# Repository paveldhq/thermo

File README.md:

# thermo
Open project for thermo cam based on ESP32 and MLX90640

`thermo.sh` options:
 - `reset` - resets all internal arduino and php state and re-downloads needed content
 - `build` - builds sketch

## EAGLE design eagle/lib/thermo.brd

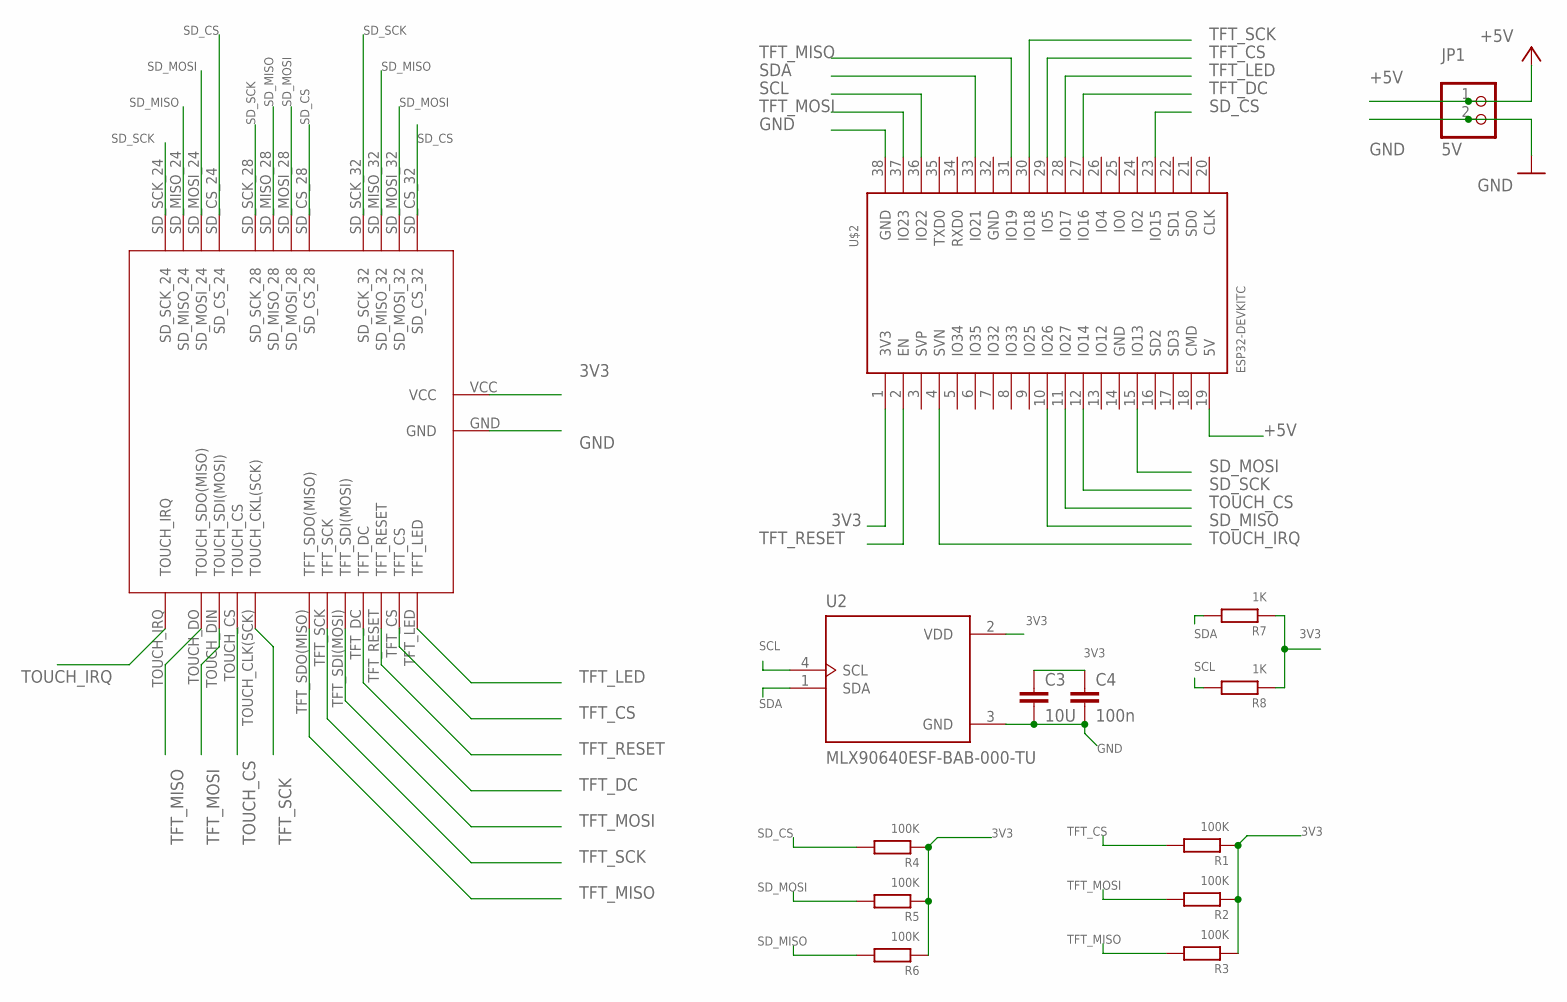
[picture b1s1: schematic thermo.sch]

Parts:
C3: 10U; C2.5-3
C4: 100n; C2.5-3
JP1: 5V; 1X02
R1, R2, R3, R4, R5, R6: 100K; 0204/7
R7, R8: 1K; 0204/7
U2: MLX90640ESF-BAB-000-TU; TO292P945H1165-4
U$2: ESP32DEVKITC; ESP32-DEVKITC
U$3: ILI9341_DISPLAY_SD_MODULE

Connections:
3V3: C3.1, C4.1, R1.1, R2.1, R3.1, R4.1, R5.1, R6.1, R7.1, R8.1, U2.2 (VDD), U$2.1 (3V3), U$3.VCC
+5V: JP1.1, U$2.19 (5V)
GND: C3.2, C4.2, JP1.2, U2.3 (GND), U$2.38 (GND), U$3.GND
SCL: R8.2, U2.4 (SCL), U$2.36 (IO22)
SDA: R7.2, U2.1 (SDA), U$2.33 (IO21)
SD_CS: R4.2, U$2.23 (IO15), U$3.SD_CS_24, U$3.SD_CS_28, U$3.SD_CS_32
SD_MISO: R6.2, U$2.10 (IO26), U$3.SD_MISO_24, U$3.SD_MISO_28, U$3.SD_MISO_32
SD_MOSI: R5.2, U$2.15 (IO13), U$3.SD_MOSI_24, U$3.SD_MOSI_28, U$3.SD_MOSI_32
SD_SCK: U$2.12 (IO14), U$3.SD_SCK_24, U$3.SD_SCK_28, U$3.SD_SCK_32
TFT_CS: R1.2, U$2.29 (IO5), U$3.TFT_CS
TFT_DC: U$2.27 (IO16), U$3.TFT_DC
TFT_LED: U$2.28 (IO17), U$3.TFT_LED
TFT_MISO: R3.2, U$2.31 (IO19), U$3.TFT_SDO(MISO), U$3.TOUCH_DO (TOUCH_SDO(MISO))
TFT_MOSI: R2.2, U$2.37 (IO23), U$3.TFT_SDI(MOSI), U$3.TOUCH_DIN (TOUCH_SDI(MOSI))
TFT_RESET: U$2.2 (EN), U$3.TFT_RESET
TFT_SCK: U$2.30 (IO18), U$3.TFT_SCK, U$3.TOUCH_CLK(SCK) (TOUCH_CKL(SCK))
TOUCH_CS: U$2.11 (IO27), U$3.TOUCH_CS
TOUCH_IRQ: U$2.4 (SVN), U$3.TOUCH_IRQ

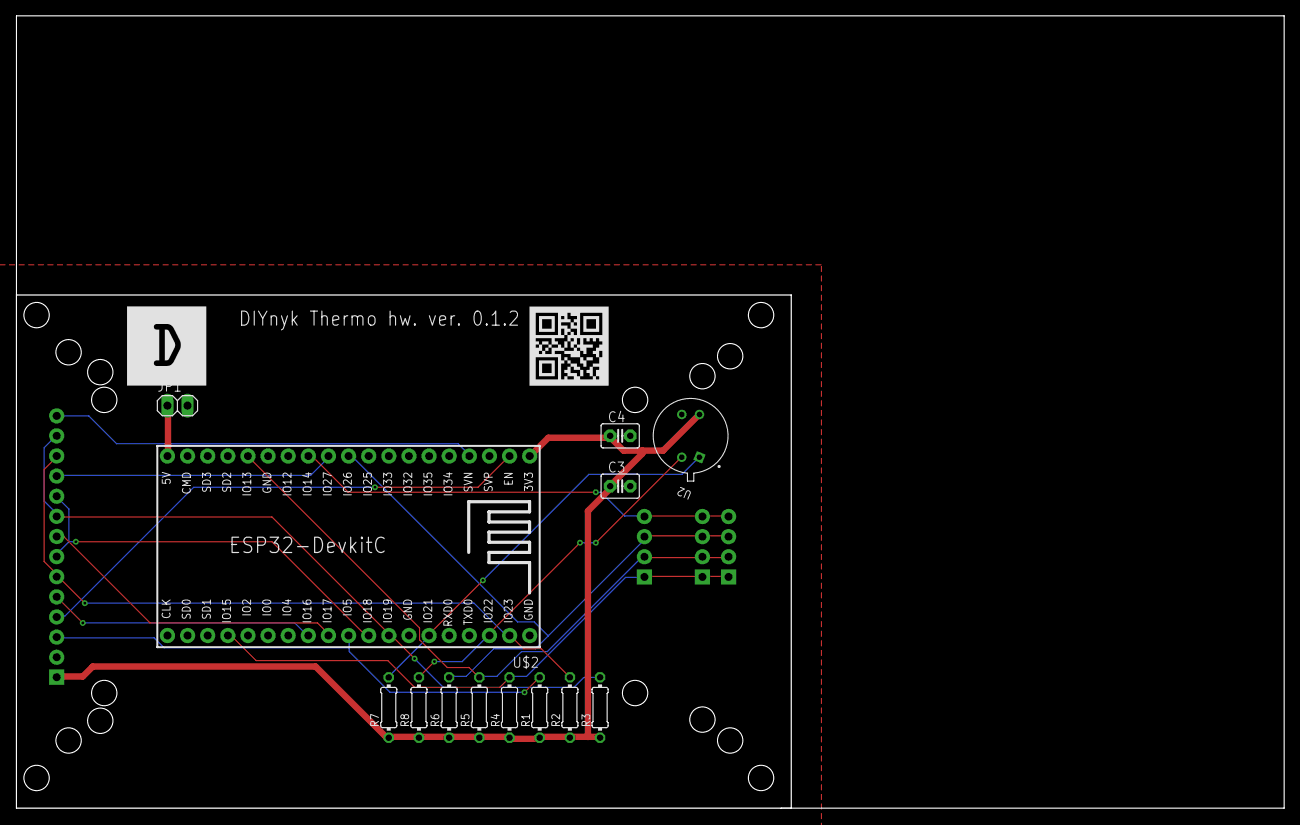
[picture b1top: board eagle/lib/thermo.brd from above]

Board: 2 copper layers, 160.0 x 100.0 mm, 16 parts (1 on the bottom side), 18 nets.

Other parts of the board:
U$1: DIYNYK_10MM
U$4: QR_10MM

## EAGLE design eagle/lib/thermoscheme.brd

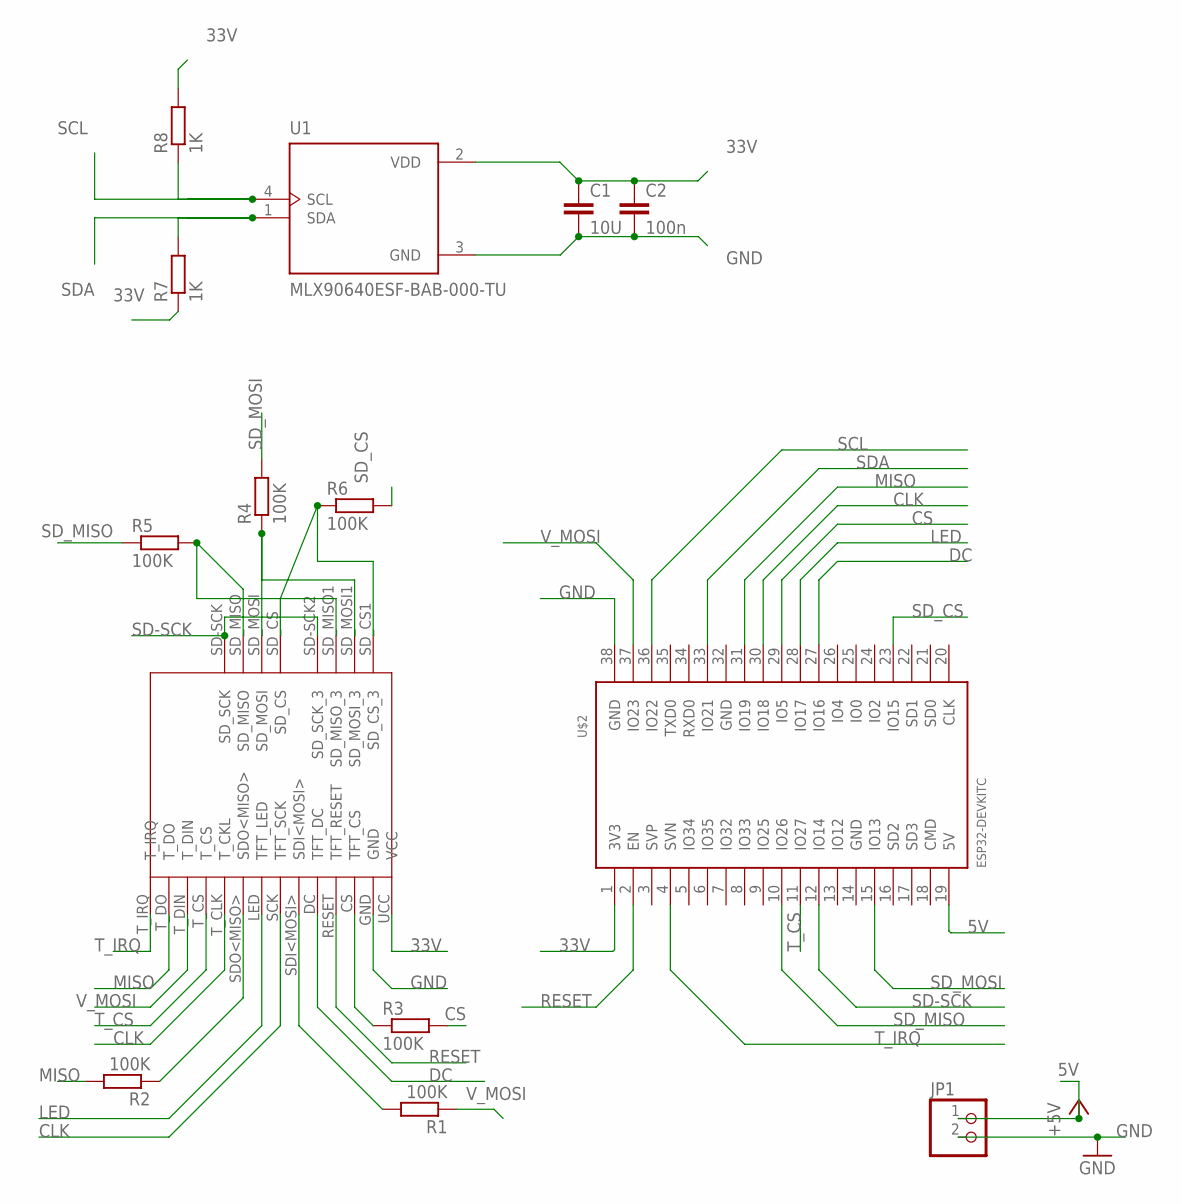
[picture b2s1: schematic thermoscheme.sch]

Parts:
C1: 10U; C2.5-3
C2: 100n; C2.5-3
JP1: PINHD-1X2; 1X02
R1, R2, R3, R4, R5, R6: 100K; 0207/10
R7, R8: 1K; 0204/7
U1: MLX90640ESF-BAB-000-TU; TO292P945H1165-4
U$2: ESP32DEVKITC; ESP32-DEVKITC
U$3: ILI9341

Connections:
5V: JP1.1, U$2.19 (5V)
33V: C1.1, C2.1, R7.1, R8.2, U1.2 (VDD), U$2.1 (3V3), U$3.UCC (VCC)
CLK: U$2.30 (IO18), U$3.SCK (TFT_SCK), U$3.T_CLK (T_CKL)
CS: R3.2, U$2.29 (IO5)
DC: U$2.27 (IO16), U$3.DC (TFT_DC)
GND: C1.2, C2.2, JP1.2, U1.3 (GND), U$2.38 (GND), U$3.GND
LED: U$2.28 (IO17), U$3.LED (TFT_LED)
MISO: R2.2, U$2.31 (IO19), U$3.T_DO
unnamed: R5.2, U$3.SD_MISO, U$3.SD_MISO1 (SD_MISO_3)
unnamed: R4.1, U$3.SD_MOSI, U$3.SD_MOSI1 (SD_MOSI_3)
unnamed: R6.1, U$3.SD_CS, U$3.SD_CS1 (SD_CS_3)
unnamed: R2.1, U$3.SDO<MISO>
unnamed: R3.1, U$3.CS (TFT_CS)
unnamed: R1.2, U$3.SDI<MOSI>
RESET: U$2.2 (EN), U$3.RESET (TFT_RESET)
SCL: R8.1, U1.4 (SCL), U$2.36 (IO22)
SD-SCK: U$2.12 (IO14), U$3.SD-SCK (SD_SCK), U$3.SD-SCK2 (SD_SCK_3)
SDA: R7.2, U1.1 (SDA), U$2.33 (IO21)
SD_CS: R6.2, U$2.23 (IO15)
SD_MISO: R5.1, U$2.10 (IO26)
SD_MOSI: R4.2, U$2.15 (IO13)
T_CS: U$2.11 (IO27), U$3.T_CS
T_IRQ: U$2.4 (SVN), U$3.T_IRQ
V_MOSI: R1.1, U$2.37 (IO23), U$3.T_DIN

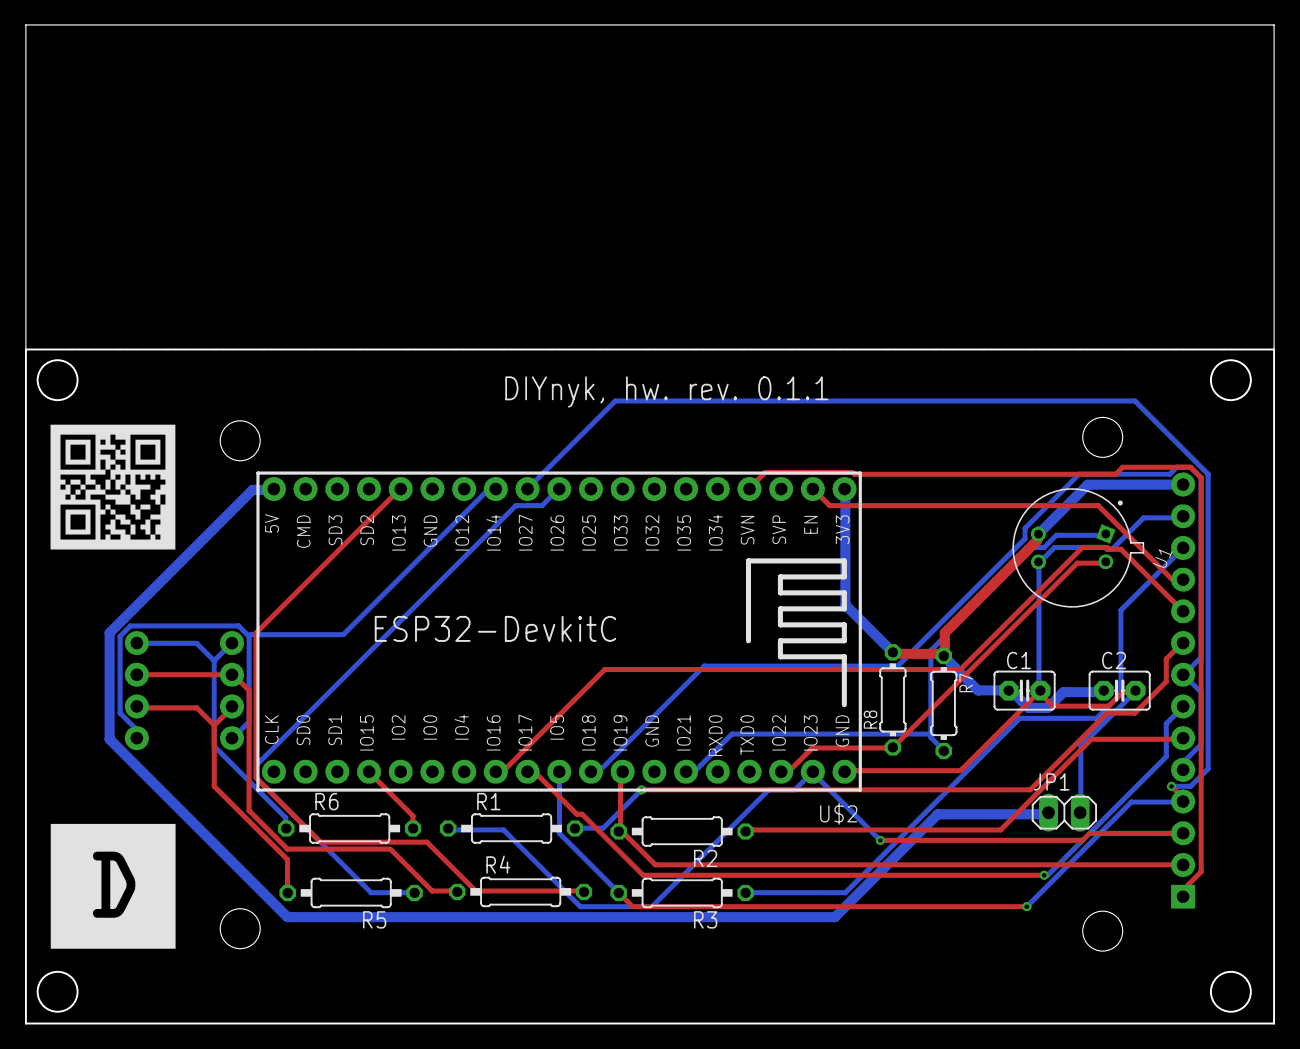
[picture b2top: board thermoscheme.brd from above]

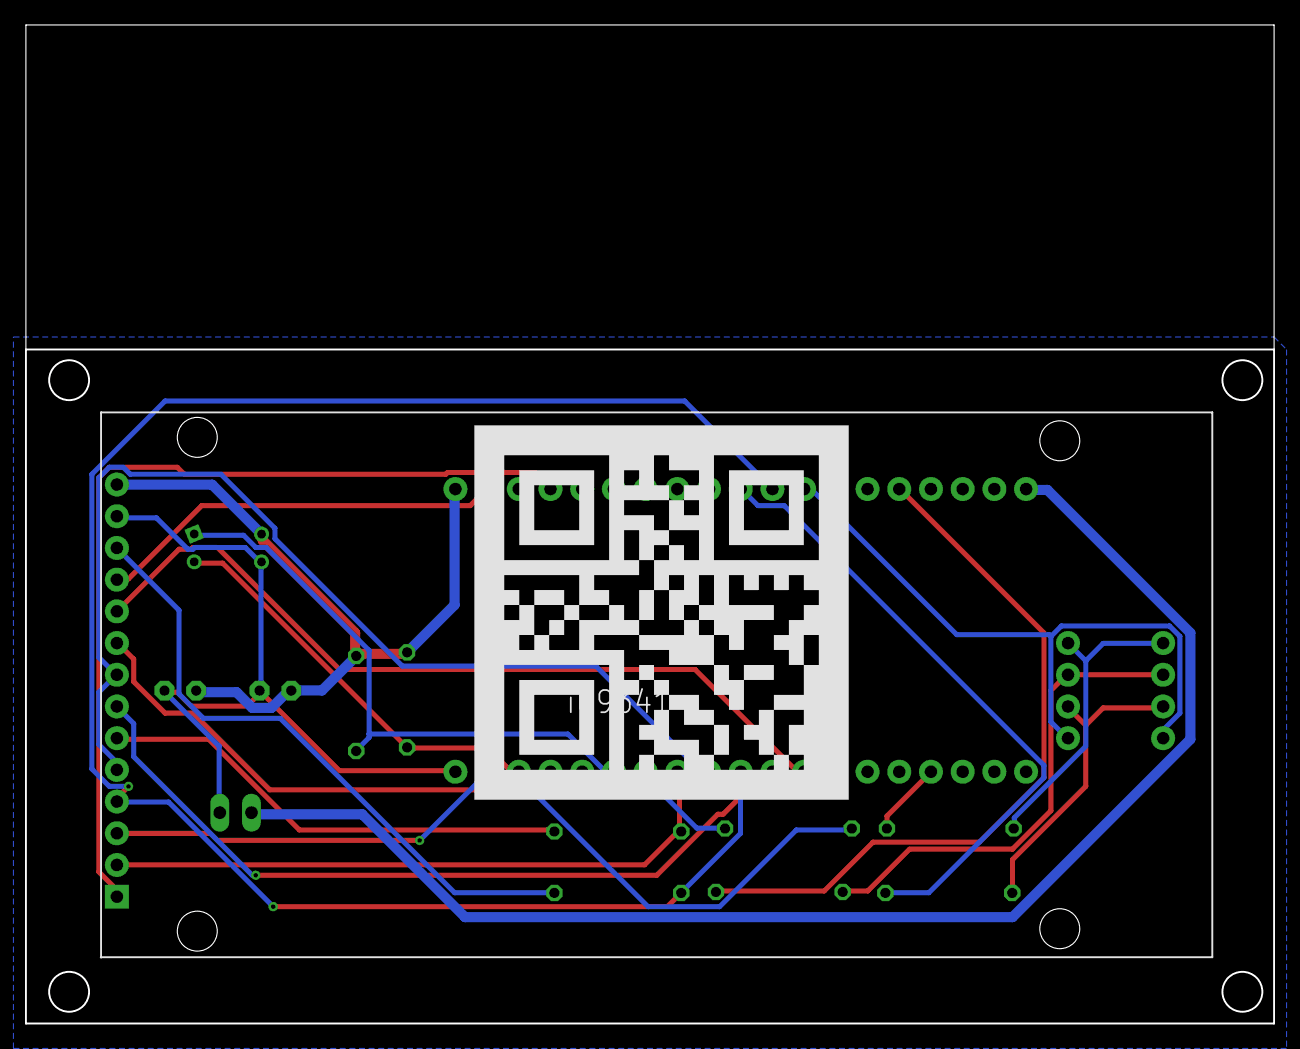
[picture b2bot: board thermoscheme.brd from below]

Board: 2 copper layers, 100.0 x 80.0 mm, 17 parts (2 on the bottom side), 24 nets.

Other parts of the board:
U$1: QR_30MM
U$4: QR_10MM
U$5: DIYNYK_10MM

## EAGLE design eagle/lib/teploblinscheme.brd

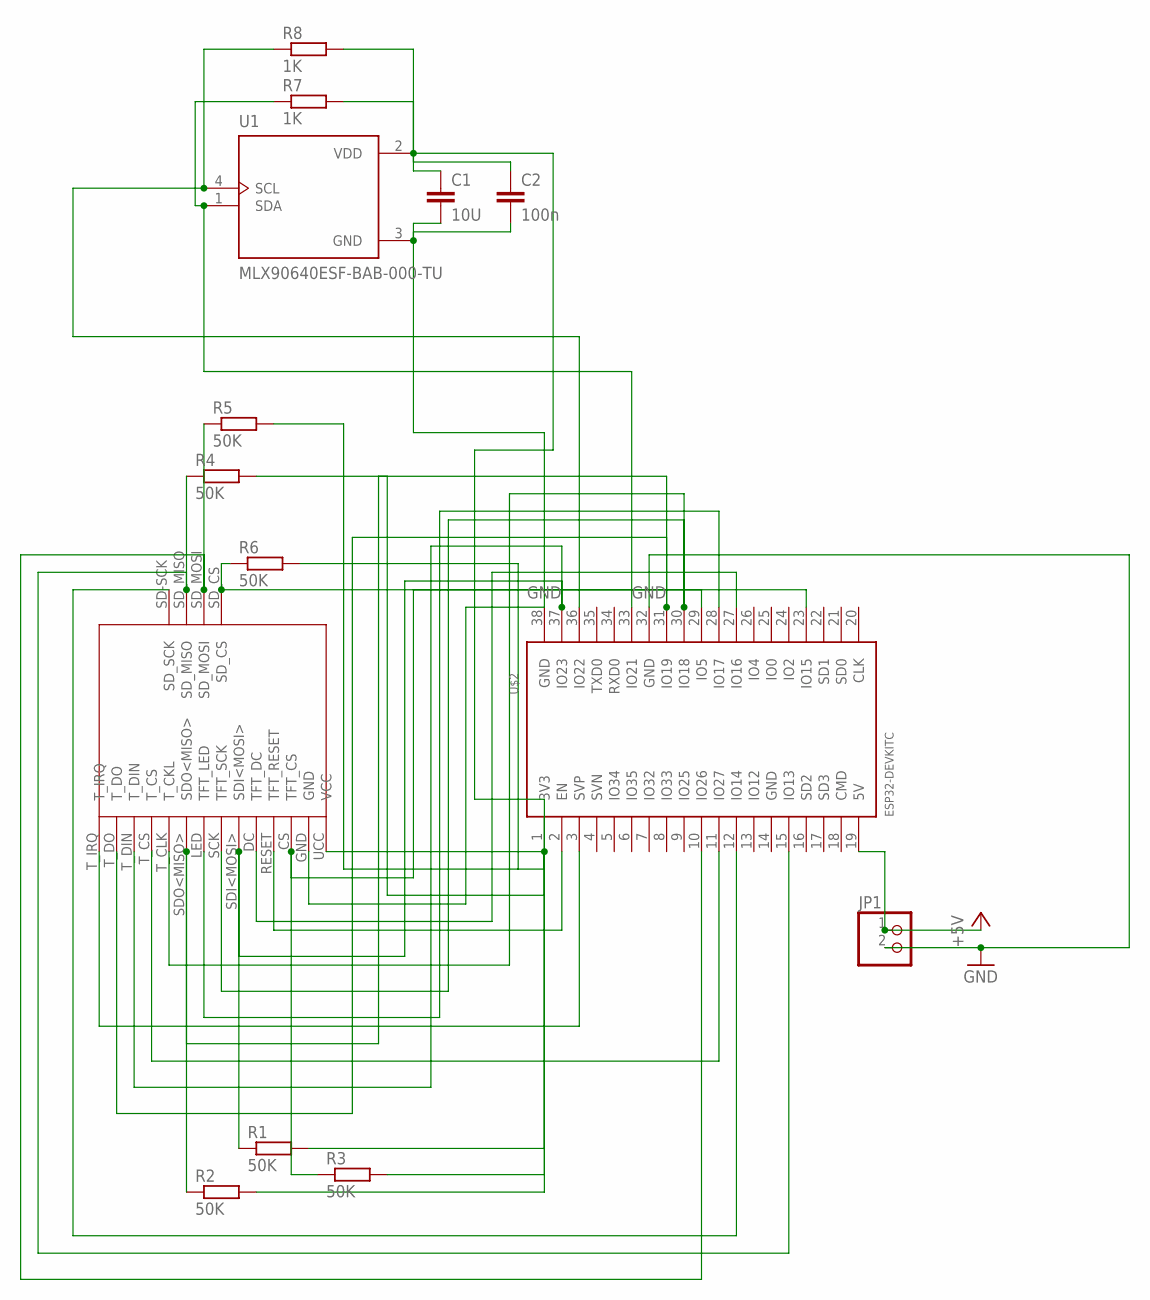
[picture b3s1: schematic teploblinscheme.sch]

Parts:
C1: 10U; C2.5-3
C2: 100n; C2.5-3
JP1: PINHD-1X2; 1X02
R1, R2, R3, R4, R5, R6: 50K; 0207/10
R7, R8: 1K; 0204/7
U1: MLX90640ESF-BAB-000-TU; TO292P945H1165-4
U$1: ILI9341; SKR1
U$2: ESP32DEVKITC; ESP32-DEVKITC

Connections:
+5V: JP1.1, U$2.19 (5V)
GND: C1.2, C2.2, JP1.2, U1.3 (GND), U$2.32 (GND)
unnamed: U$1.SCK (TFT_SCK), U$1.T_CLK (T_CKL), U$2.30 (IO18)
unnamed: R1.2, R2.2, R3.2, R4.2, R5.2, R6.2, U$1.UCC (VCC), U$2.1 (3V3)
unnamed: U$1.LED (TFT_LED), U$2.28 (IO17)
unnamed: R3.1, U$1.CS (TFT_CS), U$2.29 (IO5)
unnamed: U$1.RESET (TFT_RESET), U$2.2 (EN)
unnamed: U$1.DC (TFT_DC), U$2.27 (IO16)
unnamed: R1.1, U$1.SDI<MOSI>, U$1.T_DIN, U$2.37 (IO23)
unnamed: R2.1, U$1.SDO<MISO>, U$1.T_DO, U$2.31 (IO19)
unnamed: U$1.GND, U$2.38 (GND)
unnamed: R4.1, U$1.SD_MISO, U$2.15 (IO13)
unnamed: U$1.T_CS, U$2.11 (IO27)
unnamed: R5.1, U$1.SD_MOSI, U$2.10 (IO26)
unnamed: R6.1, U$1.SD_CS, U$2.23 (IO15)
unnamed: U$1.T_IRQ, U$2.3 (SVP)
unnamed: R8.1, U1.4 (SCL), U$2.36 (IO22)
unnamed: C1.1, C2.1, R7.2, R8.2, U1.2 (VDD)
unnamed: R7.1, U1.1 (SDA), U$2.33 (IO21)
unnamed: U$1.SD-SCK (SD_SCK), U$2.12 (IO14)

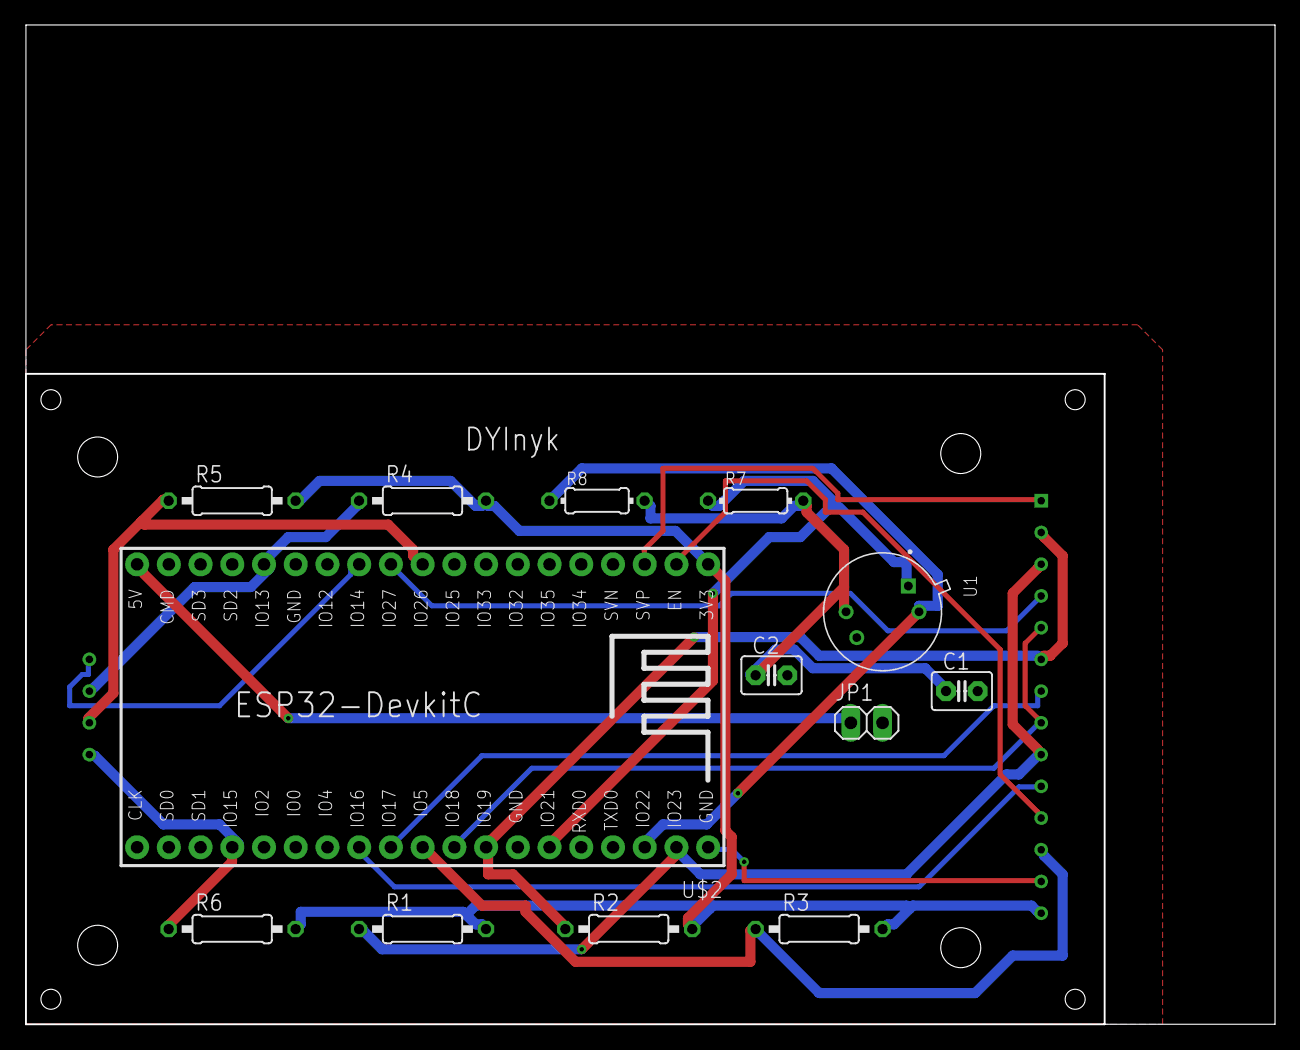
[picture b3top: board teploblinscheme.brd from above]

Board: 2 copper layers, 100.0 x 80.0 mm, 14 parts (1 on the bottom side), 20 nets.

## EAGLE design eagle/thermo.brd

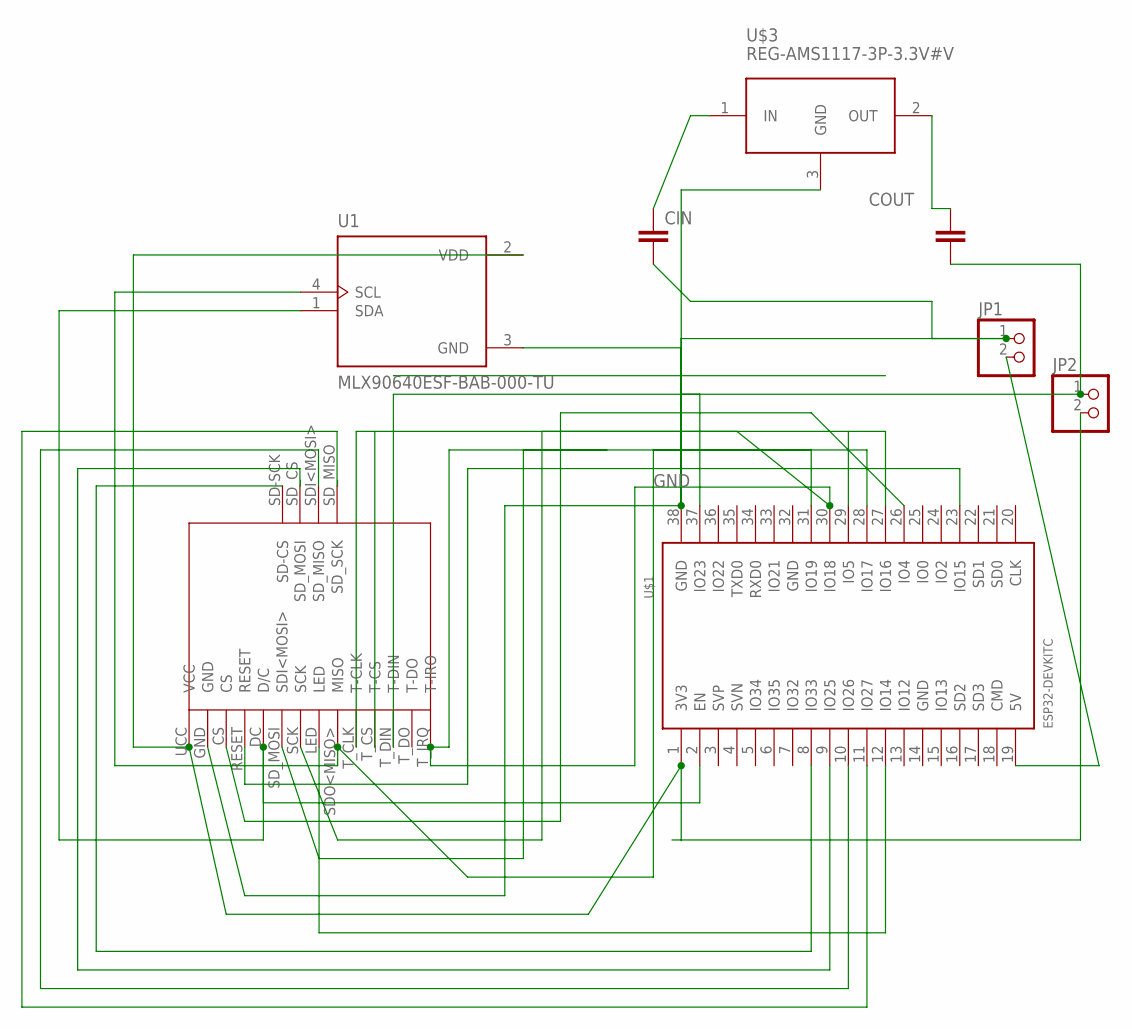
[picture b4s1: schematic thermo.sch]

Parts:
CIN: C2.5/2; C2.5-2
COUT: C2.5/2; C2.5-2
JP1, JP2: PINHD-1X2; 1X02
U1: MLX90640ESF-BAB-000-TU; TO292P945H1165-4
U$1: ESP32DEVKITC; ESP32-DEVKITC
U$2: TFT.SPI.240X320; SKR1
U$3: REG-AMS1117-3P-3.3V#V; REG-AMS1117-3P#V

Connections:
GND: CIN.2, COUT.2, JP1.1, JP2.1, U1.3 (GND), U$1.38 (GND), U$2.GND, U$3.3 (GND)
unnamed: JP1.2, U$1.19 (5V)
unnamed: JP2.2, U1.2 (VDD), U$1.1 (3V3), U$2.UCC (VCC)
unnamed: U1.4 (SCL), U$1.31 (IO19), U$2.SDO<MISO> (MISO)
unnamed: U$1.37 (IO23), U$2.T_DIN (T-DIN)
unnamed: U$1.26 (IO4), U$2.CS
unnamed: U1.1 (SDA), U$1.2 (EN), U$2.DC (D/C)
unnamed: U$1.23 (IO15), U$2.RESET
unnamed: U$1.12 (IO14), U$2.LED
unnamed: U$1.8 (IO33), U$2.SD-SCK (SD-CS)
unnamed: U$1.28 (IO17), U$1.30 (IO18), U$2.SCK, U$2.T_IRQ (T-IRO)
unnamed: CIN.1, U$3.1 (IN)
unnamed: U$1.9 (IO25), U$2.SD_CS (SD_MOSI)
unnamed: COUT.1, U$3.2 (OUT)
unnamed: U$1.10 (IO26), U$2.SDI<MOSI> (SD_MISO)
unnamed: U$1.11 (IO27), U$2.SD_MISO (SD_SCK)
unnamed: U$1.27 (IO16), U$1.29 (IO5), U$2.T_CLK (T-CLK), U$2.T_CS (T-CS)

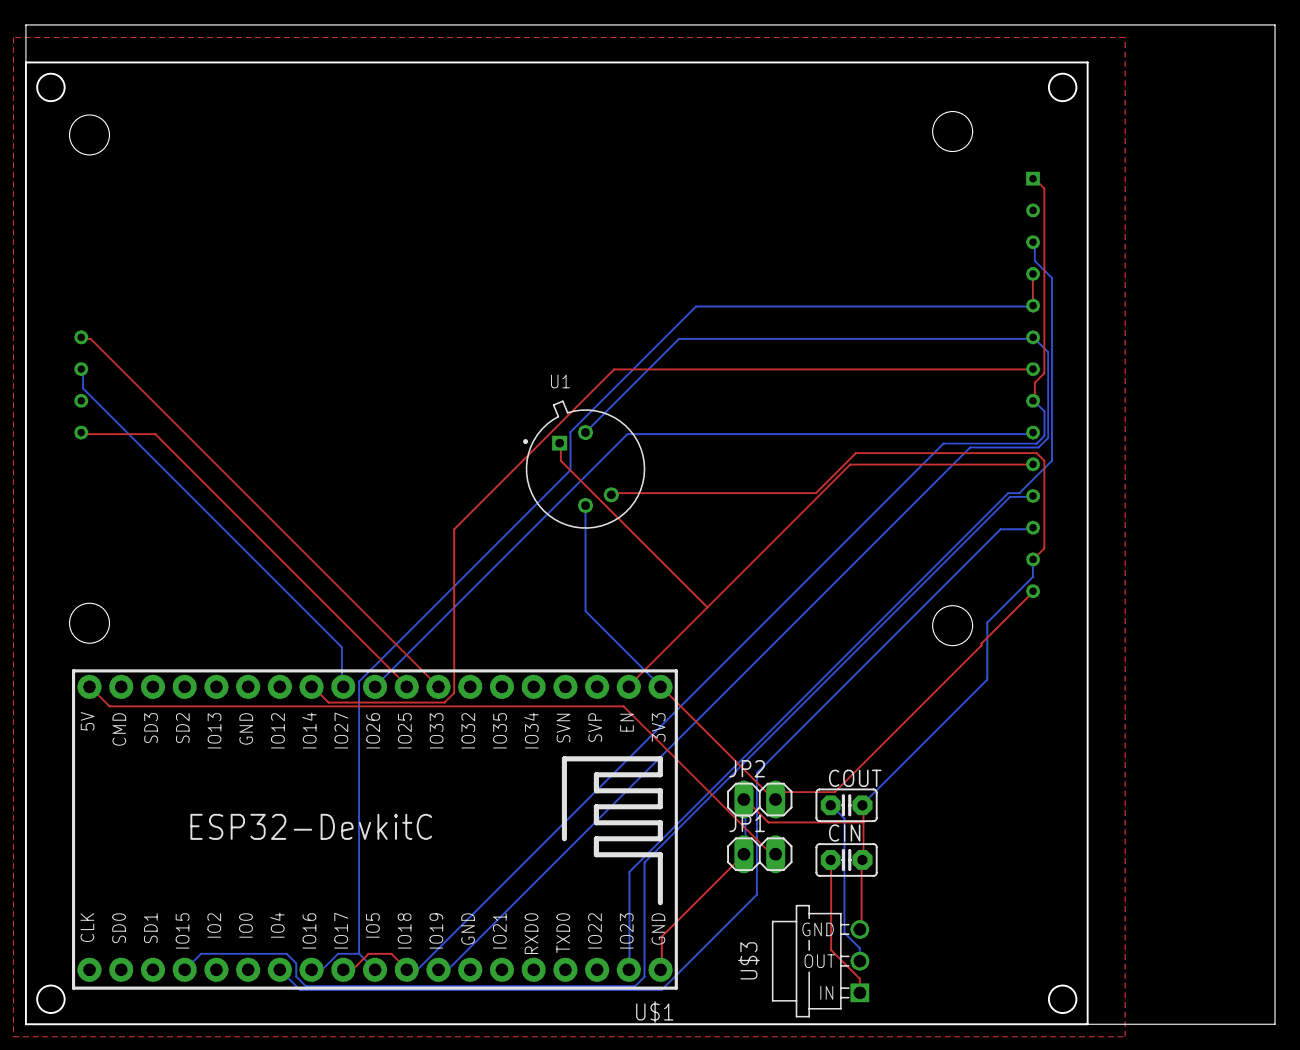
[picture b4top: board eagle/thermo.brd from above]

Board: 2 copper layers, 100.0 x 80.0 mm, 8 parts (1 on the bottom side), 17 nets.

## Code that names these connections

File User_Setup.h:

#define ILI9341_DRIVER

// https://randomnerdtutorials.com/esp32-pinout-reference-gpios/
// http://medesign.seas.upenn.edu/index.php/Guides/ESP32-pins
// https://github.com/espressif/arduino-esp32
// https://arduinomaster.ru/platy-arduino/esp32-arduino-raspinovka-arduino-ide/
// https://randomnerdtutorials.com/power-saving-latching-circuit/
// https://github.com/netzbasteln/MLX90640-Thermocam
// https://openhomeautomation.net/esp8266-battery
// https://circuits4you.com/2018/12/31/esp32-pwm-example/
//https://lastminuteengineers.com/handling-esp32-gpio-interrupts-tutorial/


#define LED 17
#define TFT_MISO 19
#define TFT_MOSI 23
#define TFT_SCLK 18
#define TFT_CS   5 // Chip select control pin
#define TFT_DC    16 // Data Command control pin
//#define TFT_RST   15  // Reset pin (could connect to RST pin)
#define TOUCH_CS 27     // Chip select pin (T_CS) of touch screen
#define T_IRQ 39
#define SD_CS 15
//SD_Mosi 13
//SD_Miso 26
//SD_csk 14

#define LOAD_GLCD   // Font 1. Original Adafruit 8 pixel font needs ~1820 bytes in FLASH
#define LOAD_FONT2  // Font 2. Small 16 pixel high font, needs ~3534 bytes in FLASH, 96 characters
#define LOAD_FONT4  // Font 4. Medium 26 pixel high font, needs ~5848 bytes in FLASH, 96 characters
#define LOAD_FONT6  // Font 6. Large 48 pixel font, needs ~2666 bytes in FLASH, only characters 1234567890:-.apm
#define LOAD_FONT7  // Font 7. 7 segment 48 pixel font, needs ~2438 bytes in FLASH, only characters 1234567890:-.
#define LOAD_FONT8  // Font 8. Large 75 pixel font needs ~3256 bytes in FLASH, only characters 1234567890:-.
#define LOAD_GFXFF  // FreeFonts. Include access to the 48 Adafruit_GFX free fonts FF1 to FF48 and custom fonts

// Comment out the #define below to stop the SPIFFS filing system and smooth font code being loaded
// this will save ~20kbytes of FLASH
#define SMOOTH_FONT

// With an ILI9341 display 40MHz works OK, 80MHz sometimes fails


#define SPI_FREQUENCY  40000000// Actually sets it to 26.67MHz = 80/3
#define SPI_TOUCH_FREQUENCY  2500000

//#define USE_HSPI_PORT



//вставить под воид сетап что б заработал лед ->
//-> pinMode(LED, OUTPUT);
//-> digitalWrite(LED, HIGH); 
//
///uint16_t calData[5] = { 441, 3324, 301, 3406, 7 };
  //tft.setTouch(calData);    тач  

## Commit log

2020-02-14 Add eagle TFT library
2020-02-14 added alpha version of rest description
2020-02-14 Add open-api description
2020-02-14 removed temporary file
2020-02-16 added wifi settings manager wrapper
2020-02-18 updated tags
2020-02-21 click-test
2020-03-02 Added - env setup scripts - php-based cli to write small logic
2020-03-02 tuning
2020-03-03 Generalize code
2020-03-06 implemented ` ./cli/app.sh ext-lib:install` command to install any public repo from github as arduino library
2020-03-09 at last it is building :)
2020-03-10 Voltage regulator datasheet
2020-03-10 button click class
2020-03-15 small final fixes before running builds on travis
2020-03-15 fix permissions
2020-03-15 chmod added
2020-03-15 run docker as `travis` user, not root
2020-03-15 fix typo
2020-03-15 added check for empty string
2020-03-15 improved logging updated curl flags fixed messages
2020-03-15 add exit code
2020-03-15 added build status badge
2020-03-17 Добавлены необходимые устройства в библиотеку
2020-03-20 display symbol fix
2020-03-22 Исправлена библиотека экрана(сд пины).Сделана принципиальная схема и печатная плата.
2020-04-15 Created folder examples and creature interrupts_touch_example, ledBlinkExample
2020-04-17 scheme_eagle
2020-04-21 камера поменял
2020-04-21 gerber
2020-05-01 added thermal code + user-serup
2020-05-01 DIYnyk 0.1.1
2020-05-15 removed old
2020-05-15 Fixed library
2020-05-15 Added design blocks
2020-05-15 Updated scheme
2020-05-16 ledBlink
2020-05-20 Updated scheme 0.0.2
2020-05-21 Fixed scheme 0.1.2
2020-05-22 comleted
2021-01-25 User_setup.h дополнен

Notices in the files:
parts and their libraries:
teploblinEkran: Released under the Creative Commons Attribution 4.0 International License: http://creativecommons.org/licenses/by/4.0
